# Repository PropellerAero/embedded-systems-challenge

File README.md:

# Propeller Embedded Systems Challenge

This is a small design task similar to the problems tackled by the Propeller hardware team. We want to see how you approach open ended problems and what you learn along the way. We are more interested in your process and critical thinking than the final result. If there is any ambiguity, make a note of any assumptions made and questions you would ask to resolve them.

## Background

Propeller Aero has recently decided to get into the consumer smart home devices market. Why? We have no idea, but it seemed like a good idea at the time. We've just finished designing the first product in this range, the Propeller LampMate™ and are eager to start manufacturing.

The LampMate is a small table lamp, it features:

- USB-C Power input
- WiFi control
- A warm white LED
- Not much else!

## The task

In this repository you will find the following design files for the LampMate main circuit board:

- `PropellerLampMate/` - The KiCAD EDA design project
- `PropellerLampMate.pdf` - The schematic drawing
- `PropellerLampMate_gerber/` - The PCB design in Gerber format
- `PropellerLampMate.png`- A 3D rendering of the layout

### Part A

This design has 10 intential errors in the schematic drawing and 8 in the PCB layout. Find as many as you can and write a couple of sentences for each explaining the problem, what impact it will have and how it should be fixed. Document these issues in whatever format you prefer (document, slide deck, marked up drawings) - focus on being as clear and succinct as possible.

### Part B

When we begin manufacturing the LampMate, the production team will need a programming and test procedure for this PCB. Device firmware will need to be loaded on to the microcontroller and the assembled PCB will need to be tested to ensure there are no assembly errors and it functions as expected.

Draw up a high-level design for a test including:

- A block diagram of any test fixture hardware required
- A process flow digram including the automated and manual steps to take freshly assembled PCBs in and output programmed and tested boards ready for final assembly
- Brief notes on each component and step

Consider in your design:

- Where will test points be required on the LampMate PCB to facilitate programming and testing?
- Which steps can be automated and which must be performed manually by an operator?
- How can we ensure the device functions as expected when the customer receives it?
- What kinds of assembly errors are likely? How can we catch these?
- How can we make this process as simple and fast as possible to minimise cost?

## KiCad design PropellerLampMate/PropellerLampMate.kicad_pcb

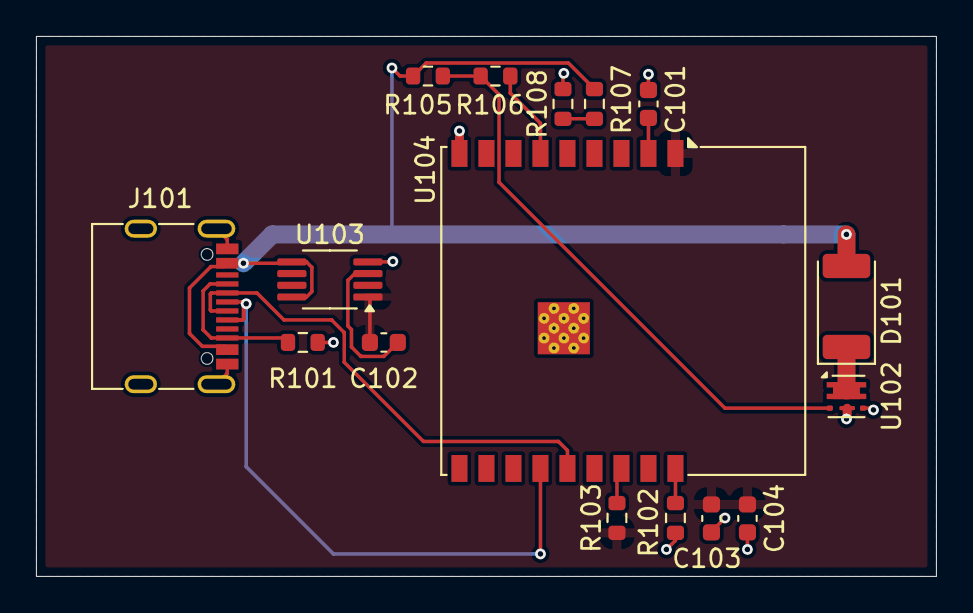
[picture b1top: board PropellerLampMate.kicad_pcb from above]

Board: 2 copper layers, 50.0 x 30.0 mm, 16 parts (0 on the bottom side), 14 nets.

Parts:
C101, C103: 1uF; C_0603_1608Metric
C102: 10nF; C_0603_1608Metric
C104: 100nF; C_0603_1608Metric
D101: LED; LED_2010_5025Metric
J101: USB_C_USB2.0; USB_C_Receptacle_G-Switch_GT-USB-7010ASV
R101: 5.1k; R_0603_1608Metric
R102, R103, R105: 10k; R_0603_1608Metric
R106: 22; R_0603_1608Metric
R107: 20k; R_0603_1608Metric
R108: 120k; R_0603_1608Metric
U102: SiA462DJ; Vishay_PowerPAK_SC70-6L_Single
U103: LT1762-3.3; MSOP-8_3x3mm_P0.65mm
U104: ESP32-C3-WROOM-02

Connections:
+3V3: C102.2, C103.1, C104.1, R103.1, U103.1 (OUT), U104.1 (3V3)
+5V: D101.2 (A), J101.A4 (VBUS), J101.A9 (VBUS), J101.B4 (VBUS), J101.B9 (VBUS), R105.1, R107.1, U103.5 (~SHDN), U103.8 (IN)
/LED_EN: R106.1, U104.6 (IO7)
/USB_D+: J101.A6 (D+), J101.B6 (D+), U104.13 (USB_D-)
/USB_D-: J101.A7 (D-), J101.B7 (D-), U104.14 (USB_D+)
/Vcc_scaled: R107.2, R108.1, U104.4 (IO5_ADC)
/~RST: C101.1, U104.2 (EN)
GND: C101.2, C103.2, C104.2, J101.A1 (GND), J101.A12 (GND), J101.B1 (GND), J101.B12 (GND), J101.S1 (SHIELD), R101.2, R102.1, R108.2, U102.4 (S), U103.4 (GND), U104.9 (GND), U104.19 (GND)
unnamed: D101.1 (K), U102.1 (D)
unnamed: J101.A5 (CC1), J101.B5 (CC2), R101.1
unnamed: R105.2, R106.2, U102.3 (G)
unnamed: C102.1, U103.3 (BYP)
unnamed: R102.2, U104.18 (IO0)
unnamed: R103.2, U104.16 (IO2)

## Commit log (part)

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2024-12-09 Add reference PCB
2024-12-09 Add PDF / PNG / Gerbers
2024-12-09 Add readme
2024-12-09 Add missing slash
2026-01-12 [DEP-1351] [skip ci] Adding Propeller Github standard files
    As part of SOC2 compliance we have implemented enforcement of standard files,
    including checks to ensure all GitHub Pull Requests are linked to a Jira card
    as a way to meet our obligation of always having changes documented and
    approved.
